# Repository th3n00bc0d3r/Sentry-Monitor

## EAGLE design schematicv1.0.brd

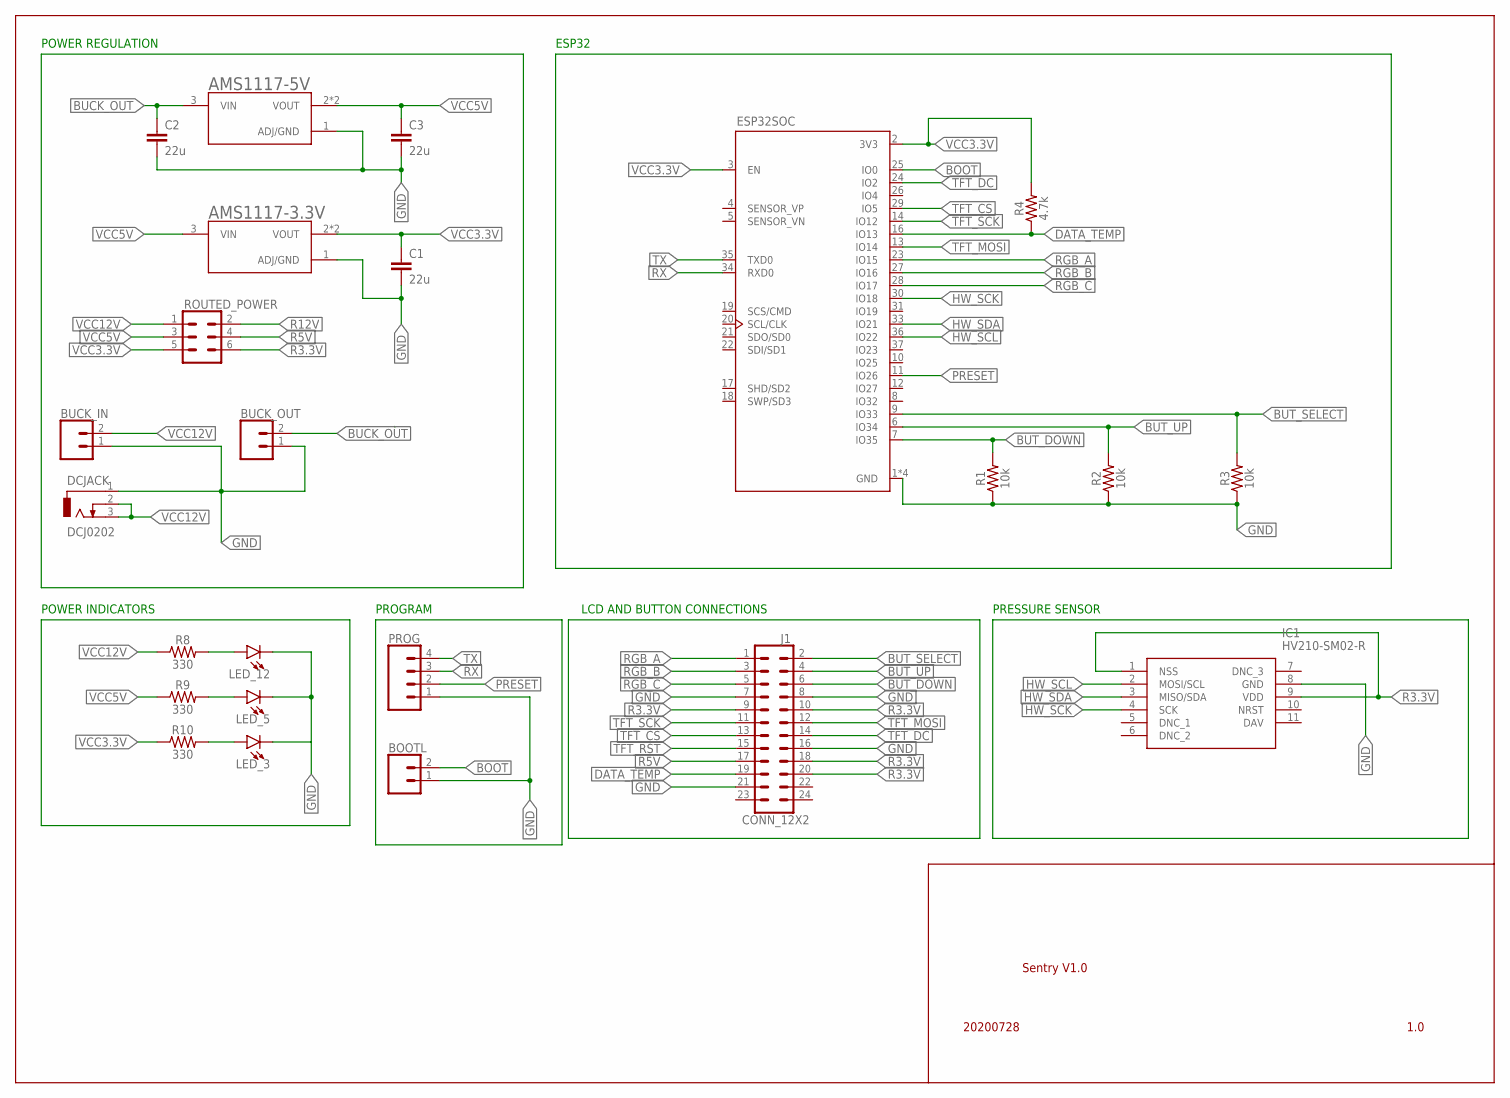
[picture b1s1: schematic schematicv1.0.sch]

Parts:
AMS1117-3.3V, AMS1117-5V: AMS1117; SOT229P700X180-4N
BOOTL: CONN_02; 1X02
BUCK_IN: CONN_02; 1X02
BUCK_OUT: CONN_02; 1X02
C1, C2, C3: 22u; 1206
DCJACK: DCJ0202
ESP32SOC: ESP32-WROOM-32D; MODULE_ESP32-WROOM-32D
IC1: HV210-SM02-R; HV210SM02R
J1: CONN_12X2; 2X12
LED_3, LED_5, LED_12: LED1206; LED-1206
PROG: CONN_04PTH; 1X04
R1, R2, R3: 10k; 1206
R4: 4.7k; 1206
R8, R9, R10: 330; 1206
ROUTED_POWER: CONN_03X2FEMALE; 2X3

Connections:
BOOT: BOOTL.2, ESP32SOC.25 (IO0)
BUCK_OUT: AMS1117-5V.3 (VIN), BUCK_OUT.2, C2.1
BUT_DOWN: ESP32SOC.7 (IO35), J1.6, R1.2
BUT_SELECT: ESP32SOC.9 (IO33), J1.2, R3.2
BUT_UP: ESP32SOC.6 (IO34), J1.4, R2.2
DATA_TEMP: ESP32SOC.16 (IO13), J1.19, R4.1
GND: AMS1117-3.3V.1 (ADJ/GND), AMS1117-5V.1 (ADJ/GND), BOOTL.1, BUCK_IN.1, BUCK_OUT.1, C1.2, C2.2, C3.2, DCJACK.1, ESP32SOC.1 (GND), ESP32SOC.15 (GND), ESP32SOC.38 (GND), ESP32SOC.39 (GND), IC1.8 (GND), J1.7, J1.8, J1.16, J1.21, LED_3.C, LED_5.C, LED_12.C, PROG.1, R1.1, R2.1, R3.1
HW_SCK: ESP32SOC.30 (IO18), IC1.4 (SCK)
HW_SCL: ESP32SOC.36 (IO22), IC1.2 (MOSI/SCL)
HW_SDA: ESP32SOC.33 (IO21), IC1.3 (MISO/SDA)
unnamed: LED_12.A, R8.2
unnamed: LED_5.A, R9.2
unnamed: LED_3.A, R10.2
PRESET: ESP32SOC.11 (IO26), PROG.2
R3.3V: IC1.1 (NSS), IC1.9 (VDD), J1.9, J1.10, J1.18, J1.20, ROUTED_POWER.6
R5V: J1.17, ROUTED_POWER.4
R12V: ROUTED_POWER.2
RGB_A: ESP32SOC.23 (IO15), J1.1
RGB_B: ESP32SOC.27 (IO16), J1.3
RGB_C: ESP32SOC.28 (IO17), J1.5
RX: ESP32SOC.34 (RXD0), PROG.3
TFT_CS: ESP32SOC.29 (IO5), J1.13
TFT_DC: ESP32SOC.24 (IO2), J1.14
TFT_MOSI: ESP32SOC.13 (IO14), J1.12
TFT_RST: J1.15
TFT_SCK: ESP32SOC.14 (IO12), J1.11
TX: ESP32SOC.35 (TXD0), PROG.4
VCC3.3V: AMS1117-3.3V.2 (VOUT), AMS1117-3.3V.4 (VOUT), C1.1, ESP32SOC.2 (3V3), ESP32SOC.3 (EN), R4.2, R10.1, ROUTED_POWER.5
VCC5V: AMS1117-3.3V.3 (VIN), AMS1117-5V.2 (VOUT), AMS1117-5V.4 (VOUT), C3.1, R9.1, ROUTED_POWER.3
VCC12V: BUCK_IN.2, DCJACK.2, DCJACK.3, R8.1, ROUTED_POWER.1

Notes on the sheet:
POWER INDICATORS
POWER REGULATION
PROGRAM
LCD AND BUTTON CONNECTIONS
PRESSURE SENSOR
ESP32
Sentry V1.0
20200728
1.0

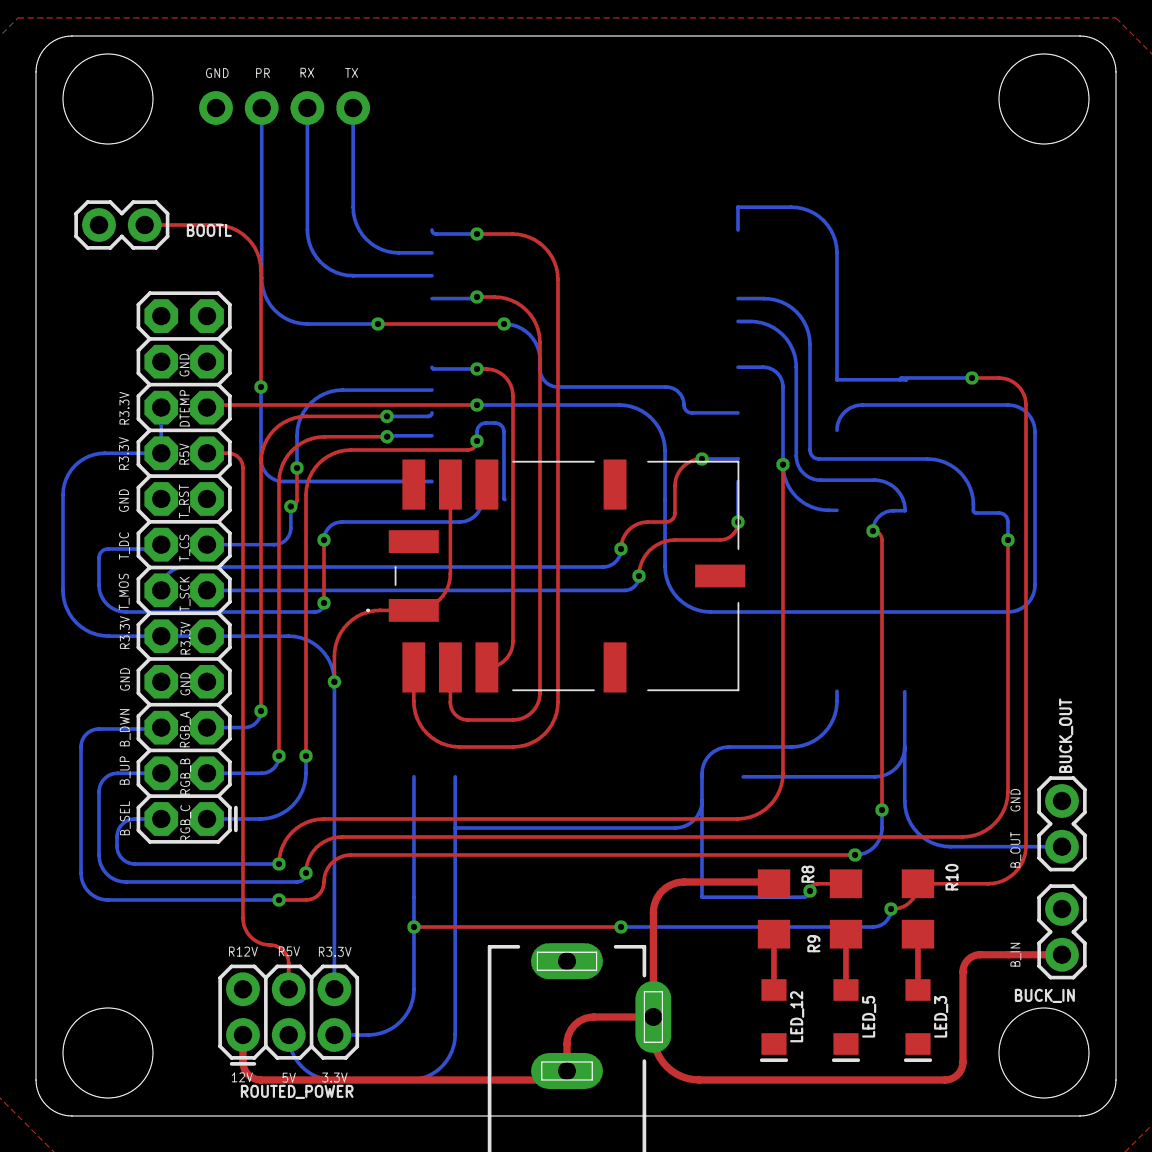
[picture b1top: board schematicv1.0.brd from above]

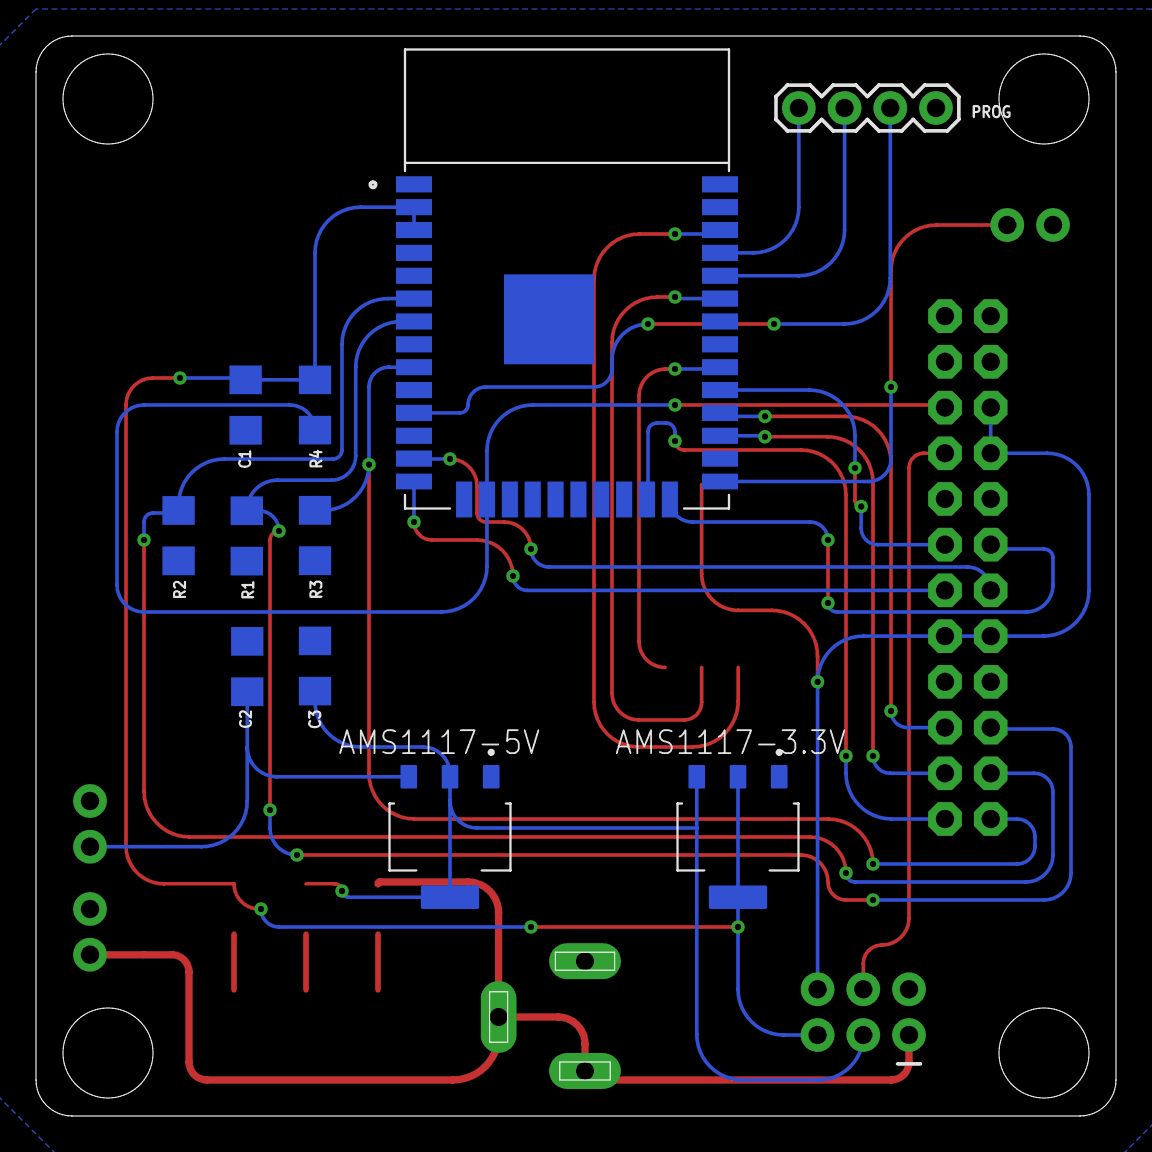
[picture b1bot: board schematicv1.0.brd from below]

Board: 2 copper layers, 60.0 x 60.0 mm, 24 parts (11 on the bottom side), 28 nets.

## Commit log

2020-07-28 Step File Added

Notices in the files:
parts and their libraries:
SparkFun-Connectors: Licensing: Creative Commons ShareAlike 4.0 International - https://creativecommons.org/licenses/by-sa/4.0
